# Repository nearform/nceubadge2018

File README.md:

# The NodeConf EU 2018 Badge

## Changing your name on the badge

This was the top request during NodeConf EU so we've made it as easy as possible. Just [go here](https://nodebadge.org/name/) and follow the simple instructions.

## Quick Links

- [GitHub Repo](https://github.com/nearform/nceubadge2018)
- [Espruino Bluetooth Getting Started](http://www.espruino.com/Quick+Start+BLE#pixljs)
- [Espruino Pixl.js info](http://www.espruino.com/Pixl.js)
- [Monday's Bluetooth Workshop](https://gfwilliams.github.io/workshop-nodeconfeu2018/)
- [Returning your badge to normal](#returning-to-standard)
- [The Badge's default firmware](https://github.com/nearform/nceubadge2018/blob/master/js/badge.js)

Please submit PRs for any apps or backlight patterns you created in:

- [Apps](https://github.com/nearform/nceubadge2018/tree/master/apps)
- [Patterns](https://github.com/nearform/nceubadge2018/tree/master/patterns)

To add them to your badge, connect with the IDE then copy and paste
them into the left-hand side of the IDE.

## Getting Started

The badge is based on a [Pixl.js](http://www.espruino.com/Pixl.js), so a
lot of the tutorials and information there still apply.

The button names can be hard to read because of the badge surround, but they
are as follows:

```
  ......                      ......
      ___________________________
BTN1 |                           | BTN2
     |                           |
     |                           |
     |                           |
BTN4 |___________________________| BTN3
                  ::::
```

There is an on/off slider switch on th rear of the badge just by the USB connector
(which is used for charging only).

## Bugs!

- On some of the badges, the vibration caused by the vibration motors during startup can
  cause the LED controller to stop working. If when you power your badge on it _doesn't_ go
  through all the colours of the rainbow, power it on with your thumbs over the vibration motors
  at the bottom left and right of the screen.
- If your badge stops animating while in badge mode, try just pressing a button
  and it should spring back to life (updating the actual Espruino firmware can fix
  this - see [Updating Espruino](#updating-espruino) below).
- When you charge the badge via USB, the on/off switch on the back needs to be
  set to ON (with the sticky-out part nearest the USB connector) or the battery
  won't charge.
- If you're writing bits of code using `require("Storage").write('.boot...')`
  you may eventually get errors about not being able to write (the same can happen
  when trying to change settings). You can solve this by following the
  [Returning your badge to normal](#returning-to-standard) instructions -
  but [Updating Espruino](#updating-espruino) can stop it happening again as well.

## Connecting

To avoid a complete free-for-all, when the badges start with the Nodeconf badge software
they disable the ability to connect to them. To connect, you must do one of:

- Go to the `Make Connectable` menu item
- Power the badge off, and power it on with `BTN2` or `BTN3` held down. The badge
  firmware will be loaded, but your badge will be connectable.
- (Not recommended) Power the badge off, and power it on with `BTN1` held down while the bootloader
  percent bar goes to the end, **then release when told. Do not keep holding the button
  down or all saved badge code will be erased.**. This initialises a self
  test, which will fail (because the board isn't quite a standard Pixl.js). This
  will start your badge without loading any of the badge code.

You can then use the Chrome web Browser on any Windows 10 or Mac OS device
and go to <a href="https://www.espruino.com/ide" target="_blank">espruino.com/ide</a> and you can connect.
You're looking for a device called `Pixl abcd` where `abcd` are the last 4
characters of the MAC address shown on the Badge's screen.

\*If you used Espruino before, ensure that the `Save on Send` option in the
`Communications` part of the Web IDE's settings is set to `To RAM` otherwise
you'll overwrite the badge firmware.\*\*

Check out the notes for Monday's [Bluetooth Workshop](https://gfwilliams.github.io/workshop-nodeconfeu2018/)
for more information.

### Using your own Editor

You can use the Espruino CLI:

```
npm install -g espruino

# abcd = last 4 digits displayed on your badge
espruino -d abcd --config RESET_BEFORE_SEND=false -w filename.js
```

The `-w filename,js` option watches that file for changes, so the connection
to the badge (and REPL) will be maintained and every time you save the file
in your editor it'll automatically upload.

In this case the CLI tool will upload to RAM without resetting the device,
so writing an app like this will allow you to quickly test your code:

```
Badge.apps["My App"] = ()=>{
 // Reset everything on the badge to a known state
 Badge.reset();
 // Display a menu
 Pixl.menu({ "": { "title": "-- A Test --" },
   "LED1 on" : ()=>LED1.write(1),
   "LED1 off" : ()=>LED1.write(0),
   "Back to Badge":Badge.badge
  });
};
// automatically run app for testing
Badge.apps["My App"]();
```

## Returning to Standard

- <a href="https://www.espruino.com/ide/?codeurl=https://raw.githubusercontent.com/nearform/nceubadge2018/master/js/badge.js" target="_blank">Click this link</a> in Chrome
- Change `Badge.NAME = ...` to `["Your", "Name"]` - each array element is a new line
- Connect to your badge (see above)
- If you're having trouble connecting, power your badge on with `BTN1` held down for ~10 seconds (until a message about code being erased is shown) - this will remove all code from the badge and make it connectable - ready for you to re-upload the badge code.
- Optional: Type `require("Storage").eraseAll()` in the left hand side of the IDE. This will remove all data from nonvolatile storage.
- Turn the `Save on Send` option in the `Communications` part of the Web IDE's settings to `Direct To Flash`
- Upload the code
- Return the `Save on Send` option in the `Communications` part of the Web IDE's settings to `To RAM` so you don't accidentally overwrite the code in the future.

You're sorted!

## Stuff to do

On the badge, you have a bunch of stuff you can use. Most of it is available via `NC`
in a global variable created by the badge software. If you're trying to
do things on your own without the badge software, use `var NC = require("nodeconfeu2018");`
first.

### Bluetooth

Check out [the Pixl.js page](http://www.espruino.com/Pixl.js) for examples.

### LED1, LED2

You can turn the LEDs on and off with `digitalWrite(LED1,1)` or `LED1.write(1)`. Use `0` to turn them off.

### RGB lighting

The badge has fancy RGB lighting. There's:

- **LEDs facing up** - Change these with `NC.ledTop([R,G,B])` or `NC.ledTop([])` to turn them off
- **LEDs facing down** - Change these with `NC.ledBottom([R,G,B])` or `NC.ledBottom([])` to turn them off
- **LCD backlight with 4 zones** - Change this with `NC.backlight([B,G,R,B,G,R,B,G,R,B,G,R])` or `NC.backlight([])` to turn them off

In the above code, `B/G/R` are numbers between 0 and 255 and represent Blue, Green and Red.

### Light sensor

LED2 can be used as an ambient light sensor - just use `NC.light()` to get
a reading between 0 and 1.

It will _definitely_ be thrown off by any light from any of the other on-badge LEDs.

### Vibration

You can use the vibration motors just like normal pins on Espruino...

```
// Use VIBL/VIBR for left and right motors

// Motor on
digitalWrite(VIBL,1);
// Motor off
digitalWrite(VIBL,0);
// Pulse motor on for 100ms
digitalPulse(VIBL,1,100);
// Pulse motor 3 times, for 100ms, with 150ms between each pulse
digitalPulse(VIBL,1,[100,150,100,150,100]);

// Or slowly ramp the speed of the motor up and down
var n = 0;
setTimeout(function cb() {
  analogWrite(VIBL,Math.sin(n));
  n+=0.01;
  if (n<Math.PI) setTimeout(cb,20);
  else digitalWrite(VIBL,0);
}, 20);
```

### Sound

The vibration motors can also be used to create (reasonably quiet) sounds.

```
analogWrite(VIBL,0.05,{freq:2000});  // Make sound!
```

There are some very simple examples at http://www.espruino.com/Making+Music
that will work on the vibration motor - just make sure that the second argument
of `analogWrite` (the duty cycle) is low enough that the vibration motor isn't
turning!

### Accelerometer

```
console.log(NC.accel());
// {x,y,z}
```

### Magnetometer

```
console.log(NC.mag());
// {x,y,z}
```

### LiPo

```
NC.getBatteryState()
// { charging:bool, standby:bool}
```

## Extending the badge

You can add your own 'Apps' or LED patterns that will display in the Badge's
memory just by adding them to the `Badge.patterns` or `Badge.apps` arrays.

Normally when you upload code from the right-hand side of the IDE it will reset
the badge (this won't remove saved code, but will stop the badge code from running).
To avoid this, either copy/paste your code from the right-hand side of the IDE
to the left, or disable the `Reset before send` option in the `Communications` part
of the Web IDE's settings.

## Patterns

Just do something like:

```
// LED patterns - each is [callback, period_in_ms]
Badge.patterns.blue=()=>{ var n=0;return [()=>{
  var c = [127,0,0];
  NC.ledTop(c);
  NC.ledBottom(c);
  NC.backlight(c.concat(c,c,c));
},0];};
```

And you can test by running `Badge.pattern("mine")`.

The above example will only be called once because it returns `0` for `period_in_ms`,
but you can easily supply a different value to be called more often:

```
Badge.patterns.green=()=>{ var n=0;return [()=>{
  n+=50;
  if (n>1536)n=0;
  NC.ledTop([0,Math.max(255-Math.abs(n-1024),0),0]);
  NC.ledBottom([0,Math.max(255-Math.abs(n-1384),0),0]);
  NC.backlight([0,Math.max(255-Math.abs(n-640),0),0,
                0,Math.max(255-Math.abs(n-512),0),0,
                0,Math.max(255-Math.abs(n-384),0),0,
                0,Math.max(255-Math.abs(n-256),0),0]);
},50];};
```

50ms is usually a good balance of battery life and smoothness.

## Apps

Just write your app to the `Badge.apps` array:

```
Badge.apps["My App"] = ()=>{
 // Reset everything on the badge to a known state
 Badge.reset();
 // Display a menu
 Pixl.menu({ "": { "title": "-- A Test --" },
   "LED1 on" : ()=>LED1.write(1),
   "LED1 off" : ()=>LED1.write(0),
   "Back to Badge":Badge.badge
  });
};
```

And you can test by running `Badge.apps["My App"]()`

To return to normal badge functionality just call `Badge.badge()` or `Badge.menu()`
to return to the menu.

## Saving...

When you upload code as described above, your function will be loaded
into RAM and will be lost when the badge is reset.

To make it persist, you can write it into a file in the badge's storage
called `.boot0`,`.boot1`,`.boot2` or `.boot3` - each one is executed in
turn on boot so you can have more than one extension at once.

```
require("Storage").write(".boot0",`
Badge=global.Badge||{};
Badge.apps=Badge.apps||{};
Badge.apps["My App"] = ()=>{
 // Reset everything on the badge to a known state
 Badge.reset();
 // Display a menu
 Pixl.menu({ "": { "title": "-- A Test --" },
   "LED1 on" : ()=>LED1.write(1),
   "LED1 off" : ()=>LED1.write(0),
   "Back to Badge":Badge.badge
  });
};
`);
```

You can also do things like overwrite the built-in name,
without having to overwrite the basic badge firmware.

```
require("Storage").write(".boot1",`
Badge=global.Badge||{};
Badge.NAME=["Hello","World"];
`);
```

## Common Pitfalls

- If you get `Badge not found` errors while trying to upload an app from the right hand side, it'll be because you're uploading with the `Reset before send` option turned on in the IDE settings (it should be turned off)
- `reset()` (or 'reset before send) removes all JS code from the badge's RAM (including the `Badge` object) - it can be handy if you want to have full control of everything on the badge. To get back, see the next point...
- If you want to get your badge firmware back out of flash memory _without_ power cycling your badge, just type `load()` in the left-hand side of the IDE
- Calling `Badge.menu()` will bring the Badge's menu back up - `Badge.badge()` goes back to displaying the badge. If you want a button in the app to bring you back to the menu, you can just call: `setWatch(Badge.menu, BTN1);`
- `Badge.reset()` attempts to reset the badge's state (removing watches and intervals) - it's an idea to stick this as the first line in your app to make sure you start from a known state each time.

## Soldering Stuff

There are some special GPIO connectors on the badge. These can be accessed with
commands like `digitalWrite(D10,1)` or `analogRead(A0)`.

- `J2` (Top Left) contains (left to right) `GND`,`D10`,`D11`,`D12`,`D13` and `3.3v`
- `J1` (Top Right) contains (left to right) `GND`,`A0`,`A1`,`A2`,`A3` and `3.3v`
- `J3` (Bottom center) contains the pinout for an ESP8266 ESP01 module. This can
  also be used for wired serial comms with the badge:

```
GND            NC    NC        D1(Badge TX)
D0(Badge RX)   D9    NC        3.3v
```

### ESP8266 Wiring

Due to a slight mirroring accident, a normal ESP8266 module has to be attached
to the FRONT of the badge, slightly covering the display:

```
  ......                      ......
      ___________________________
BTN1 |                           | BTN2
     |                           |
     |            ____           |
     |           |    |          |
BTN4 |___________|    |__________| BTN3
                 |::::|
                  ----
```

However by removing the ESP01's pins and soldering them on the other side of the
module, you can fit the ESP01 to the rear of the badge very tidily.

Once soldered you can access the internet as follows:

```
var WIFI_NAME = "...";
var WIFI_PASS = "...";
D9.set(); // power on
Serial1.setup(115200,{rx:D0,tx:D1});
var wifi = require("ESP8266WiFi_0v25").connect(Serial1, function(err) {
  if (err) throw err;
  console.log("Connecting to WiFi");
  wifi.connect(WIFI_NAME, WIFI_PASS, function(err) {
    if (err) throw err;
    console.log("Connected");
    // Now you can do something, like an HTTP request
    require("http").get("http://www.pur3.co.uk/hello.txt", function(res) {
      console.log("Response: ",res);
      res.on('data', function(d) {
        console.log("--->"+d);
      });
    });
  });
});
```

Check out [http://www.espruino.com/Internet](Espruino's page on Internet stuff)
for more info.

## Updating Espruino

The badges came with Espruino v2.00, but there have [been a few changes](https://github.com/espruino/Espruino/blob/master/ChangeLog)
to Espruino since then that have fixed:

- The badge pausing issue (caused by high Bluetooth LE traffic when scanning)
- Filesystem issues when repeatedly calling `require("Storage").write`
- Other issues

To update Espruino, just [follow the Pixl.js instructions here](http://www.espruino.com/Pixl.js#firmware-updates)
with the 'Cutting edge' build linked from [the firmware download page](http://www.espruino.com/Download#pixljs).

This'll take a few minutes, and you then need to follow the steps for [Returning your badge to normal](#returning-to-standard) - so if you're fine with everything as it is, we'd recommend that you keep version 2.00 for now.

## Changing your name on the badge in the Web IDE

As an alternative to using the [simple Web Bluetooth page](https://nearform.github.io/nceubadge2018/namechanger.html) to change the name, you can also do the following:

- On the badge, press the top left button, then select "Make Connectable" from the menu and note the last four hex digits of the address of the badge
- <a href="https://www.espruino.com/ide/?codeurl=https://raw.githubusercontent.com/nearform/nceubadge2018/master/js/namechange.js" target="_blank">Click this link</a> in Chrome to open the Online IDE with the correct code
- In that code, edit the two fields "Bob" and "Loblaw" to whatever you need.
- Click the yellow Connect button in the top left corner of the IDE
- Click "Web Bluetooth" in the pop-up
- Click your device name
- Once connected, click the "Send to Espruino" button in the middle of the IDE
- Reboot your badge and you'll see the new name

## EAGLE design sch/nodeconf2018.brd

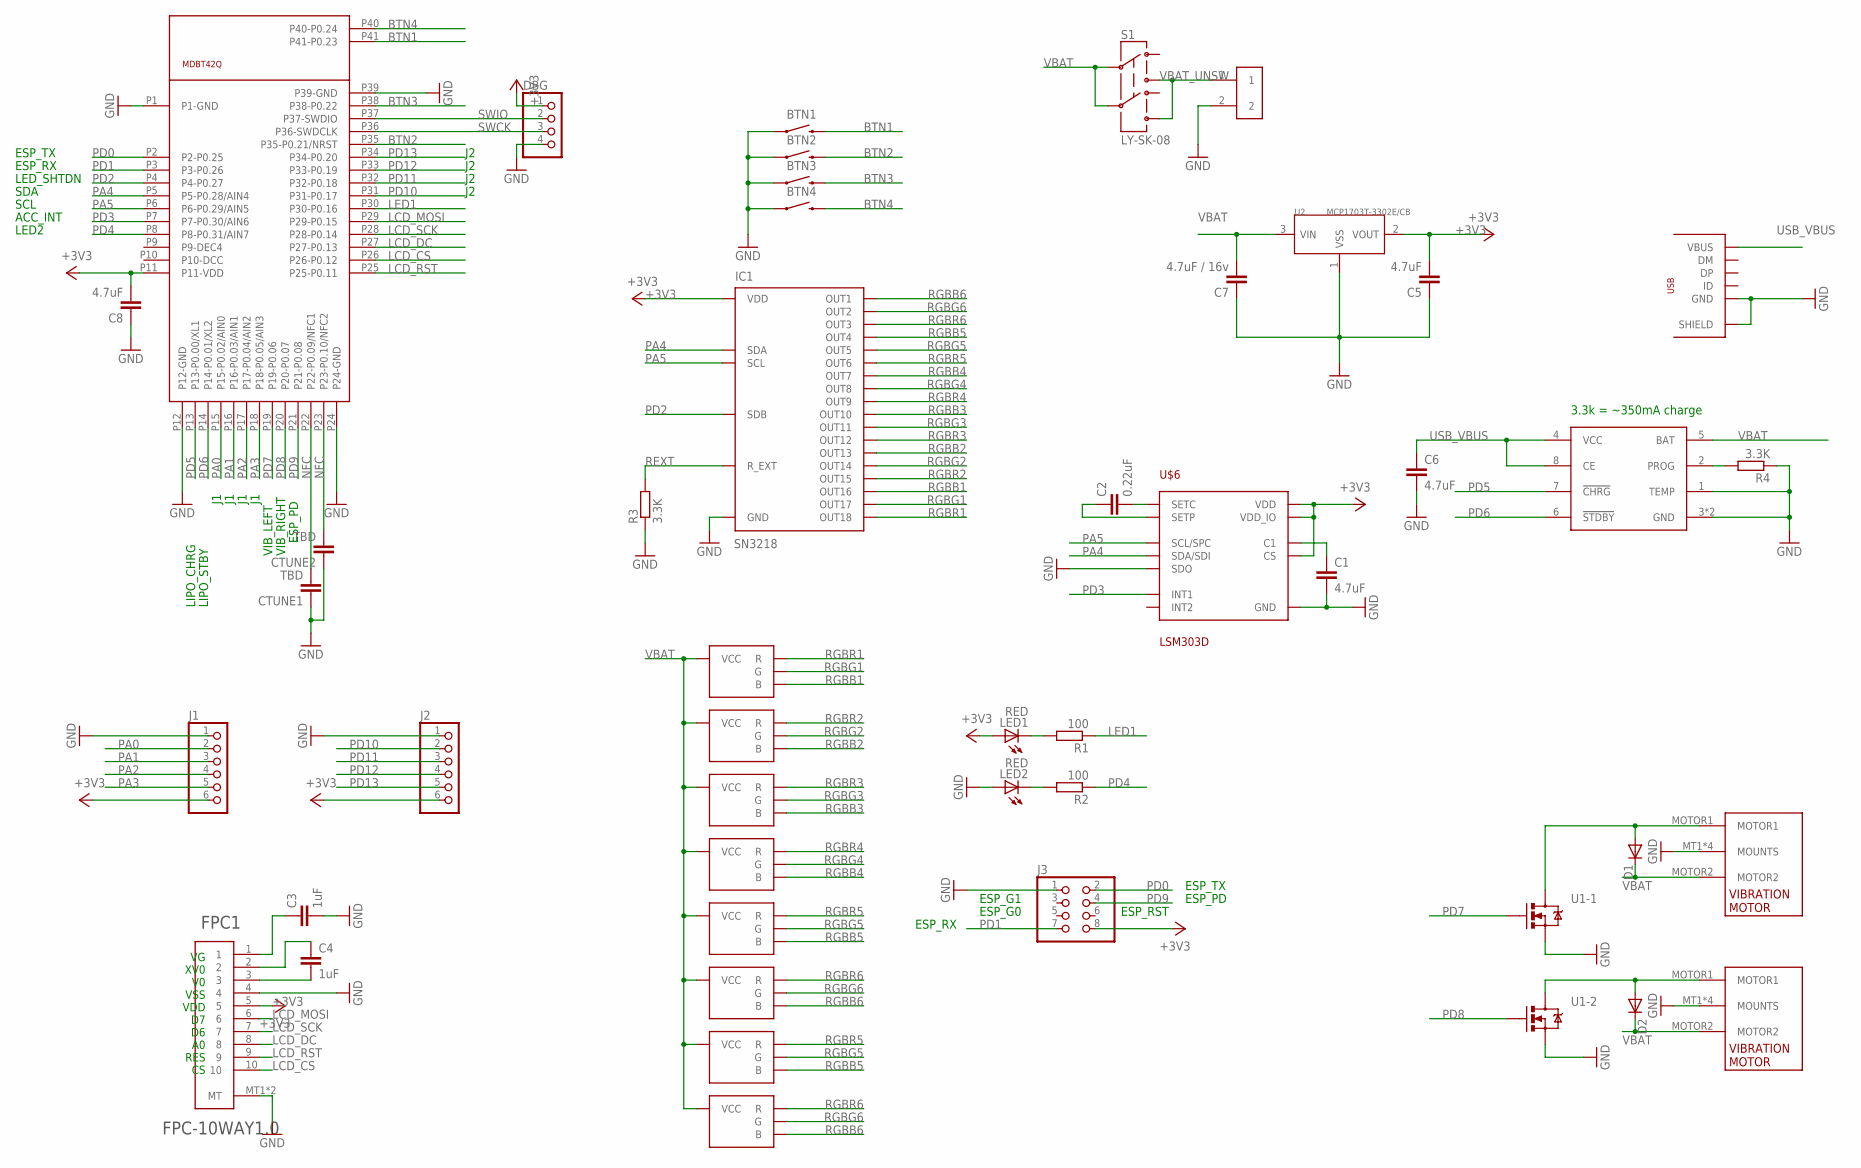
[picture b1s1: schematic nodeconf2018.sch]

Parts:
BAT: JST_2P_VERTICAL; 2P_JST_PH_VERT
BLED1, BLED2, BLED3, BLED4, BLED5, BLED6, BLED7, BLED8: 1204RGBC3ADA; APFA3010SEEZGQBDC
BTN1, BTN2, BTN3, BTN4: SWITCH-MOMENTARY-2SMD-1101NE; TACTILE-SWITCH-1101NE
C1, C5, C6: 4.7uF; C0805
C2: 0.22uF; C0603K
C3, C4: 1uF; C0603K
C7: 4.7uF / 16v; C0805
C8: 4.7uF; C0603K
CTUNE1, CTUNE2: TBD; C0603K
D1, D2: DIODE-SOD323-W; SOD323-W
DBG: PINHD-1X04_2.54-S; 1X04-S
FPC1: FPC-10WAY1.0; FPC-1.0MM-10WAY
IC1: SN3218; QFN24
J1, J2: PINHD-1X06_2.54-S; 1X06-S
J3: PINHD-2X04_2.54; 2X04
LED1, LED2: RED; CHIP-LED0603
R1, R2: 100; R0603
R3, R4: 3.3K; R0603
S1: LY-SK-08; SWITCH-DPDT
U1: MOSFET-N-DUAL; SOT563
U2: MCP1703T-3302E/CB; SOT23
U3: TP4056; SO08-PAD-300
U$1, U$2: VIBRATION_MOTOR
U$3: MDBT42Q; MDBT40
U$4: USBMICROB; MICROB-USB
U$6: LSM303D; LGA16-3MM

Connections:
+3V3: C5.2, C8.2, DBG.1, FPC1.5, IC1.3 (VDD), J1.6, J2.6, J3.8, LED1.A, U2.2 (VOUT), U$3.P11 (P11-VDD), U$6.1 (VDD_IO), U$6.8 (CS), U$6.14 (VDD)
BTN1: BTN1.2, U$3.P41 (P41-P0.23)
BTN2: BTN2.2, U$3.P35 (P35-P0.21/NRST)
BTN3: BTN3.2, U$3.P38 (P38-P0.22)
BTN4: BTN4.2, U$3.P40 (P40-P0.24)
GND: BAT.2, BTN1.1, BTN2.1, BTN3.1, BTN4.1, C1.2, C3.2, C5.1, C6.2, C7.1, C8.1, CTUNE1.1, CTUNE2.1, DBG.4, FPC1.4, FPC1.MT1 (MT), FPC1.MT2 (MT), IC1.4 (GND), IC1.GND, J1.1, J2.1, J3.1, LED2.A, R3.1, R4.1, U1.S1 (S), U1.S2 (S), U2.1 (VSS), U3.1 (TEMP), U3.3 (GND), U3.PAD (GND), U$1.MT1 (MOUNTS), U$1.MT2 (MOUNTS), U$1.MT3 (MOUNTS), U$1.MT4 (MOUNTS), U$2.MT1 (MOUNTS), U$2.MT2 (MOUNTS), U$2.MT3 (MOUNTS), U$2.MT4 (MOUNTS), U$3.P1 (P1-GND), U$3.P12 (P12-GND), U$3.P24 (P24-GND), U$3.P39 (P39-GND), U$4.GND, U$4.SH1 (SHIELD), U$4.SH2 (SHIELD), U$4.SH3 (SHIELD), U$4.SH4 (SHIELD), U$4.SH5 (SHIELD), U$4.SH6 (SHIELD), U$4.SH7 (SHIELD), U$4.SH8 (SHIELD), U$6.5 (GND), U$6.7 (SDO), U$6.10 (GND), U$6.12 (GND), U$6.13 (GND), U$6.16 (GND)
LCD_CS: FPC1.10, U$3.P26 (P26-P0.12)
LCD_DC: FPC1.8, U$3.P27 (P27-P0.13)
LCD_MOSI: FPC1.6, U$3.P29 (P29-P0.15)
LCD_RST: FPC1.9, U$3.P25 (P25-P0.11)
LCD_SCK: FPC1.7, U$3.P28 (P28-P0.14)
LED1: R1.1, U$3.P30 (P30-P0.16)
unnamed: LED1.C, R1.2
unnamed: C4.2, FPC1.3
unnamed: C4.1, FPC1.2
unnamed: LED2.C, R2.2
unnamed: C3.1, FPC1.1
unnamed: C1.1, U$6.15 (C1)
unnamed: C2.2, U$6.2 (SETC)
unnamed: C2.1, U$6.3 (SETP)
unnamed: R4.2, U3.2 (PROG)
unnamed: D2.A, U1.D2 (D), U$2.MOTOR1
unnamed: D1.A, U1.D1 (D), U$1.MOTOR1
NFC: CTUNE1.2, CTUNE2.2, U$3.P22 (P22-P0.09/NFC1), U$3.P23 (P23-P0.10/NFC2)
PA0: J1.2, U$3.P15 (P15-P0.02/AIN0)
PA1: J1.3, U$3.P16 (P16-P0.03/AIN1)
PA2: J1.4, U$3.P17 (P17-P0.04/AIN2)
PA3: J1.5, U$3.P18 (P18-P0.05/AIN3)
PA4: IC1.5 (SDA), U$3.P5 (P5-P0.28/AIN4), U$6.6 (SDA/SDI)
PA5: IC1.6 (SCL), U$3.P6 (P6-P0.29/AIN5), U$6.4 (SCL/SPC)
PD0: J3.2, U$3.P2 (P2-P0.25)
PD1: J3.7, U$3.P3 (P3-P0.26)
PD2: IC1.24 (SDB), U$3.P4 (P4-P0.27)
PD3: U$3.P7 (P7-P0.30/AIN6), U$6.11 (INT1)
PD4: R2.1, U$3.P8 (P8-P0.31/AIN7)
PD5: U3.7 (!CHRG), U$3.P13 (P13-P0.00/XL1)
PD6: U3.6 (!STDBY), U$3.P14 (P14-P0.01/XL2)
PD7: U1.G1 (G), U$3.P19 (P19-P0.06)
PD8: U1.G2 (G), U$3.P20 (P20-P0.07)
PD9: J3.4, U$3.P21 (P21-P0.08)
PD10: J2.2, U$3.P31 (P31-P0.17)
PD11: J2.3, U$3.P32 (P32-P0.18)
PD12: J2.4, U$3.P33 (P33-P0.19)
PD13: J2.5, U$3.P34 (P34-P0.20)
REXT: IC1.2 (R_EXT), R3.2
RGBB1: BLED1.2 (B), IC1.22 (OUT16)
RGBB2: BLED2.2 (B), IC1.19 (OUT13)
RGBB3: BLED3.2 (B), IC1.16 (OUT10)
RGBB4: BLED4.2 (B), IC1.13 (OUT7)
RGBB5: BLED5.2 (B), BLED7.2 (B), IC1.10 (OUT4)
RGBB6: BLED6.2 (B), BLED8.2 (B), IC1.7 (OUT1)
RGBG1: BLED1.1 (G), IC1.23 (OUT17)
RGBG2: BLED2.1 (G), IC1.20 (OUT14)
RGBG3: BLED3.1 (G), IC1.17 (OUT11)
RGBG4: BLED4.1 (G), IC1.14 (OUT8)
RGBG5: BLED5.1 (G), BLED7.1 (G), IC1.11 (OUT5)
RGBG6: BLED6.1 (G), BLED8.1 (G), IC1.8 (OUT2)
RGBR1: BLED1.3 (R), IC1.1 (OUT18)
RGBR2: BLED2.3 (R), IC1.21 (OUT15)
RGBR3: BLED3.3 (R), IC1.18 (OUT12)
RGBR4: BLED4.3 (R), IC1.15 (OUT9)
RGBR5: BLED5.3 (R), BLED7.3 (R), IC1.12 (OUT6)
RGBR6: BLED6.3 (R), BLED8.3 (R), IC1.9 (OUT3)
SWCK: DBG.3, U$3.P36 (P36-SWDCLK)
SWIO: DBG.2, U$3.P37 (P37-SWDIO)
USB_VBUS: C6.1, U3.4 (VCC), U3.8 (CE), U$4.VBUS
VBAT: BLED1.4 (VCC), BLED2.4 (VCC), BLED3.4 (VCC), BLED4.4 (VCC), BLED5.4 (VCC), BLED6.4 (VCC), BLED7.4 (VCC), BLED8.4 (VCC), C7.2, D1.C, D2.C, S1.2 (A_P), S1.5 (B_P), U2.3 (VIN), U3.5 (BAT), U$1.MOTOR2, U$2.MOTOR2
VBAT_UNSW: BAT.1, S1.1 (A_T2), S1.6 (B_T2)

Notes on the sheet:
VG XV0 V0 VSS VDD D7 D6 A0 RES CS
LED2
3.3k = ~350mA charge
SDA
SCL
ACC_INT
VIB_LEFT
VIB_RIGHT
LIPO_CHRG
LIPO_STBY
LED_SHTDN
ESP_TX
ESP_RX
ESP_PD
ESP_RST
ESP_G0
ESP_G1

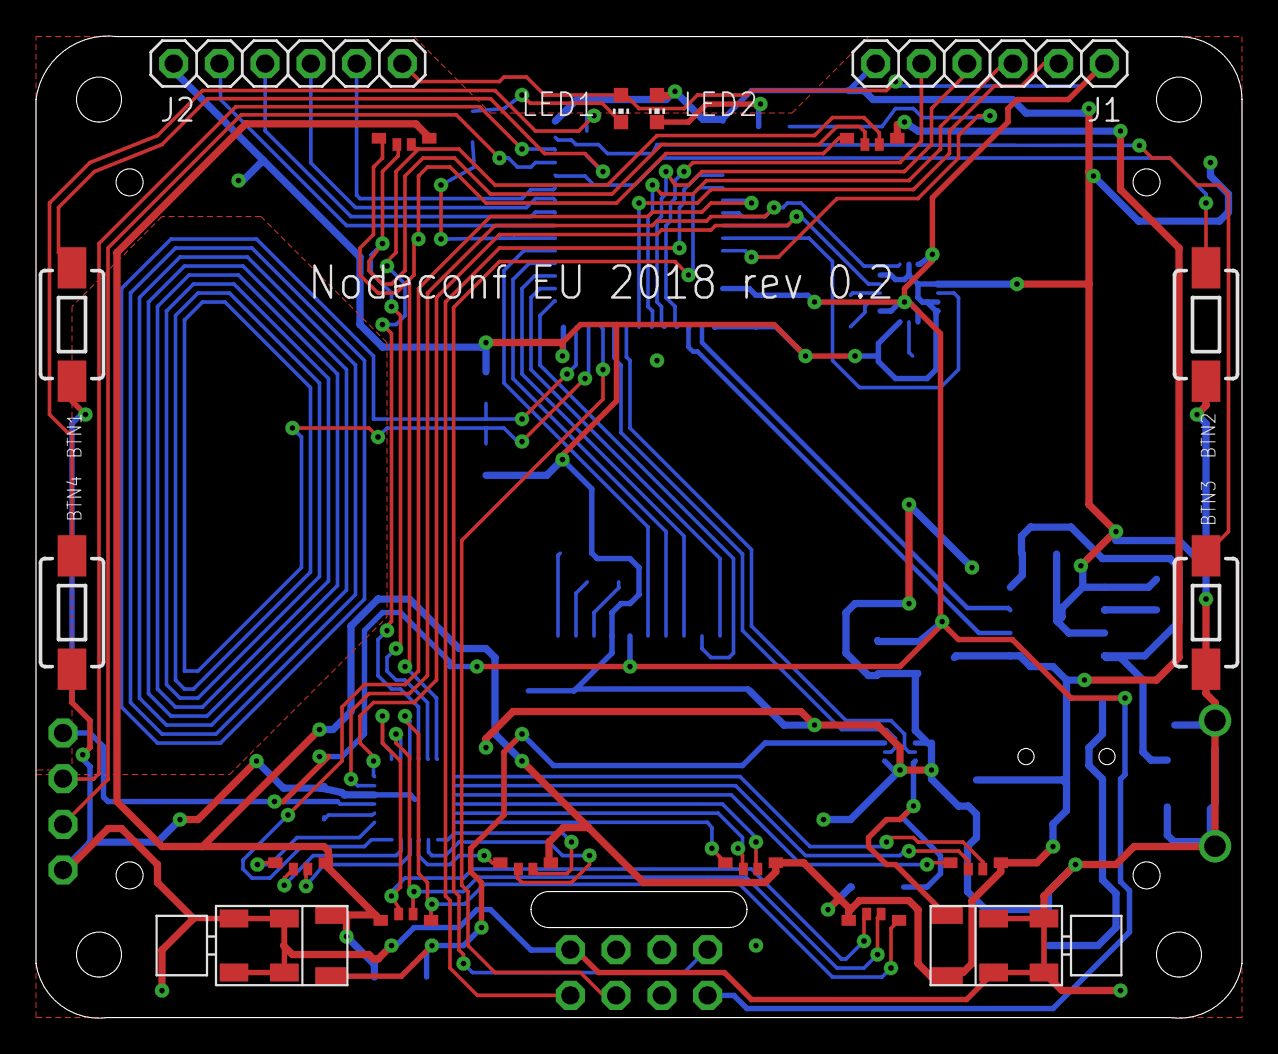
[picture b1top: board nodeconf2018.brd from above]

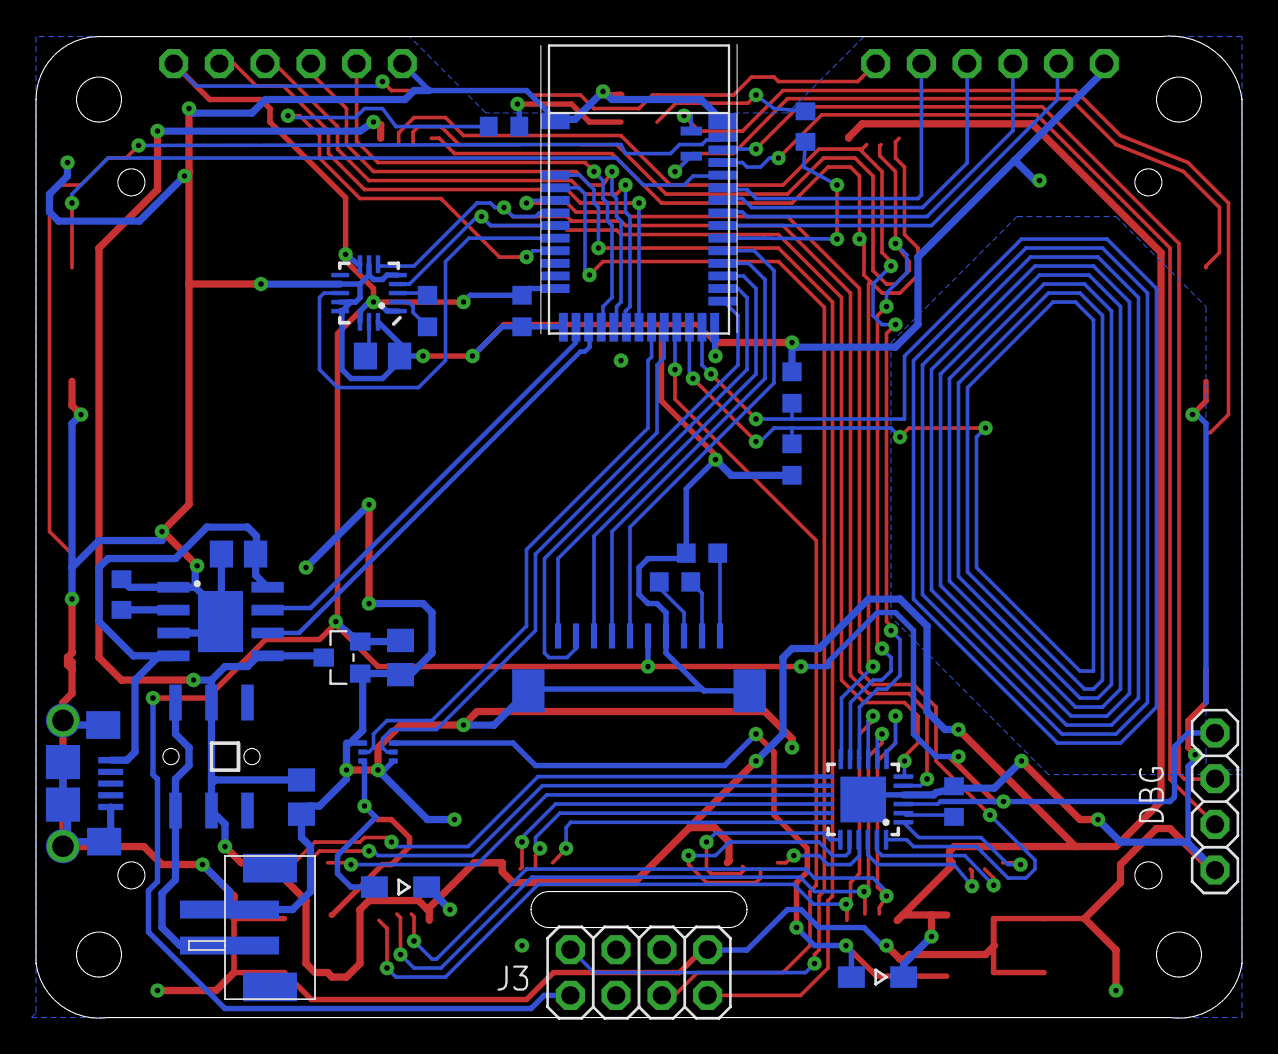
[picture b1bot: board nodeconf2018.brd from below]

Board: 2 copper layers, 67.0 x 54.6 mm, 51 parts (28 on the bottom side), 68 nets.

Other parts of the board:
U$11: 128X64_LCD_FRAME
U$12, U$13, U$14, U$15: M2.5-HOLE-WITH-MASK

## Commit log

2018-10-23 first hack at badge firmware - no Bluetooth LE listening, but custom apps & patterns
2018-10-27 scanning, image tweaks, start of workshop
2018-10-27 Added map and time functionality
2018-10-27 fix formatting
2018-10-29 Add settings page, more sane backlight choices
2018-10-29 add charge indicator
2018-10-29 fix accidental removal of onframe line - accelerometer test fns as well
2018-10-29 better accelerometer setup
2018-10-29 low battery indicator
2018-10-29 add clap detection code for getting started
2018-10-29 fix light readings
2018-10-29 notes
2018-10-29 more notes
2018-10-30 save privacy settings on exit, even if not changed
2018-10-31 remove UART for badge workshop code
2018-10-31 move ROOMS array (won't take up RAM now)
2018-10-31 move hexImage (won't take up RAM now)
2018-10-31 Compass!
2018-10-31 Now send advertising data, handle connection properly
2018-10-31 working clapometer
2018-10-31 update clap test
2018-10-31 add block read for accelerometer
2018-10-31 Add LED_COLOR handling
2018-10-31 whitlist
2018-10-31 Move NOW -> NOW1/NOW2 (same for next), and have first char as # of 10mins since 0:00
2018-10-31 now store last 3 alerts and only alert if different
2018-10-31 nice big multilingual font - for alerts and badge names
2018-10-31 use heatshrink to compress the map
2018-10-31 remove test script
2018-10-31 minor refactor
2018-11-01 Use smaller but 2x pixel font for badge, tweak bluetooth workshop example
2018-11-01 Alerts now appear over info
2018-11-01 fix badge init error
2018-11-01 allow Badge.NAME to be predefined
2018-11-01 fallback to 1x if 2x text is too wide
2018-11-01 add POC for per-user badge programming
2018-11-01 tweak connection interval change
2018-11-01 start sending notifications only after a connect
2018-11-01 check for duplicate infos
2018-11-01 trying to get scanning as fast as possible
2018-11-01 Add 'skip' option for privacy settings
2018-11-04 update docs
2018-11-04 linkage
2018-11-04 back to badge at the top of patterns
2018-11-04 default to dim rainbow backlight
2018-11-04 clear data after turning scan off
2018-11-04 automatically loop over a file full of names
2018-11-04 remove vibration on start
2018-11-04 document issues
2018-11-04 leave small gap between having the 2 motors on
2018-11-05 backlight tweaks
2018-11-05 tweaks
2018-11-05 tweak bugs list
2018-11-05 PR us your badge apps!
2018-11-06 apps/patterns
2018-11-06 espruino updates
2018-11-06 add automatic rotation based on accelerometer when in badge mode
2018-11-06 Created App for displaying name with animations
2018-11-06 pitfalls
2018-11-06 Add COC, License and basic Contrib.
2018-11-06 Add The Imperial March Tune App
2018-11-06 Update colour refs in README
2018-11-07 docs on using CLI
2018-11-11 Gordon's simple name change code so it can be invoked from online IDE
2018-11-11 Added the simple name change instructions to the README
2018-11-11 Open IDE links in new Tab
2018-11-11 fix one relative link so text can be re-used on nodeconfeubadge.org
2018-11-11 Web Bluetooth page to make Badge name changing extremely easy
2018-11-11 move namechanger file location for GH Pages
2018-11-11 improved instructions and updated README
2018-11-15 tweak text
2018-11-18 mostly working desk clock for Badge
2018-11-18 remove unnecessary rest. RAM version still not working tho
2018-11-23 added a few of Conor's Pi Zeros to the whitelist for post-NCEU demos
2018-11-27 setting up GH Pages for the mini Web Bluetooth apps
2018-11-27 latest minified code
2018-11-27 Create CNAME
2018-11-27 switching to Netlify instead of GH Pages
2018-11-27 Top level index page for webapps
2018-11-27 links to main badge site and nearform
2018-12-12 Change URL of namechanger code to nodebadge.org
2018-12-12 typo
2018-12-12 updated instructions in the comments
2019-02-05 remove quick flashing of clock code and replace with Web IDE method
2019-02-05 tweak instructions
2019-02-05 formatting
2019-10-08 add pdfs

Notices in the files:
parts and their libraries:
pimoroni: Licensing: CC v3.0 Share-Alike You are welcome to use this library for commercial purposes.
SparkFun-Electromechanical: Licensing: Creative Commons ShareAlike 4.0 International - https://creativecommons.org/licenses/by-sa/4.0
